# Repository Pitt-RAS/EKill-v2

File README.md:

# EKill-v2

This repository is part of the Pitt RAS effort for IARC Mission 7.  For an overview of the IARC competition as well as the team's efforts and technical approaches, check out our [team website](http://pittras.org/projects/IARC/), and in particular the [technical postmortem post for the project](http://pittras.org/projects/iarc/2018/08/10/update-iarc-technical-postmortem.html).

A new EKill board, slightly modifed from Liam's previous board to support more motors and handle unexpected errors on the PWM line.

To run the simulation files in Sim_Parts, you should be able to open KillSwitch2.asc from LTSpice XVII, and it should work. If you really want to understand how the logic works, the best way is to simply monitor the capacitor voltage and compare it with the PWM wave. Change the time that the PWM wave is on from 1.45 ms to 1.5 ms and back to see the timing threshold in action.

Similarly, I have the Eagle libraries organized the way they are so that anyone can simply open the main eagle project and have it just work. Though it does sacrifice some neatness.

If you want to see the parts that the footprints in the board files correspond to, open up the sole excel file in Sim_Parts.

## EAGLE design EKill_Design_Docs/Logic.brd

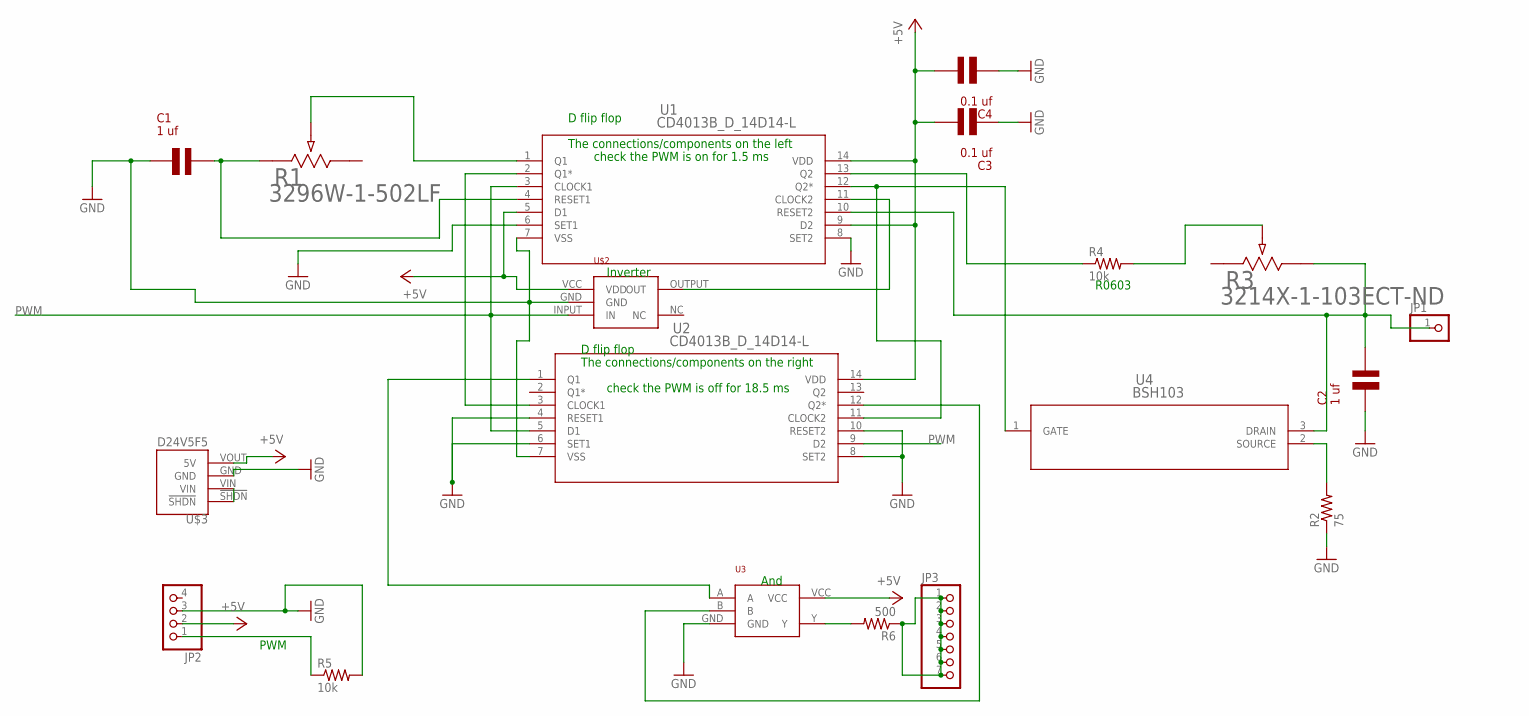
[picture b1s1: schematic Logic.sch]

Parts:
C1, C2: 1 uf; X7R0805
C3, C4: 0.1 uf; X7R0805
JP1: PINHD-1X1; 1X01
JP2: PINHD-1X4; 1X04
JP3: PINHD-1X7; 1X07
R1: 3296W-1-502LF; POT_3296W
R2: 75; R0603
R3: 3214X-1-103ECT-ND; POT_3214X
R4, R5: 10k; R0603
R6: 500; R0603
U1, U2: CD4013B_D_14D14-L; D14-L
U3: NC7SZ08-AND; NC7S04-SOT23
U4: BSH103; SOT23
U$2: NCS704-INVERTER; NC7S04-SOT23
U$3: D24V5F5; D24V5FX_FLAT_THIN_R

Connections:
+5V: C3.2, C4.2, JP2.2, U1.5 (D1), U1.9 (D2), U1.14 (VDD), U2.14 (VDD), U3.VCC, U$2.VCC (VDD), U$3.VOUT (5V)
GND: C1.1, C2.1, C3.1, C4.1, JP2.3, R2.1, R5.2, U1.6 (SET1), U1.7 (VSS), U1.8 (SET2), U2.4 (RESET1), U2.6 (SET1), U2.7 (VSS), U2.8 (SET2), U2.10 (RESET2), U3.GND, U$2.GND, U$3.GND
unnamed: R3.WIPER (2), R4.2
unnamed: C1.2, R1.1, U1.4 (RESET1)
unnamed: U1.11 (CLOCK2), U$2.OUTPUT (OUT)
unnamed: U1.2 (Q1*), U2.3 (CLOCK1)
unnamed: R4.1, U1.13 (Q2)
unnamed: R1.2, U1.1 (Q1)
unnamed: C2.2, JP1.1, R3.CW (3), U1.10 (RESET2), U4.3 (DRAIN)
unnamed: JP3.1, JP3.2, JP3.3, JP3.4, JP3.5, JP3.6, JP3.7, R6.1
unnamed: U1.12 (Q2*), U2.11 (CLOCK2), U4.1 (GATE)
unnamed: U2.1 (Q1), U3.A
unnamed: U2.12 (Q2*), U3.B
unnamed: R6.2, U3.Y
unnamed: U$3.!SHDN, U$3.VIN
unnamed: R2.2, U4.2 (SOURCE)
PWM: JP2.1, R5.1, U1.3 (CLOCK1), U2.5 (D1), U2.9 (D2), U$2.INPUT (IN)

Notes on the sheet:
Inverter
And
D flip flop
The connections/components on the left
check the PWM is on for 1.5 ms
check the PWM is off for 18.5 ms
The connections/components on the right
R0603
PWM

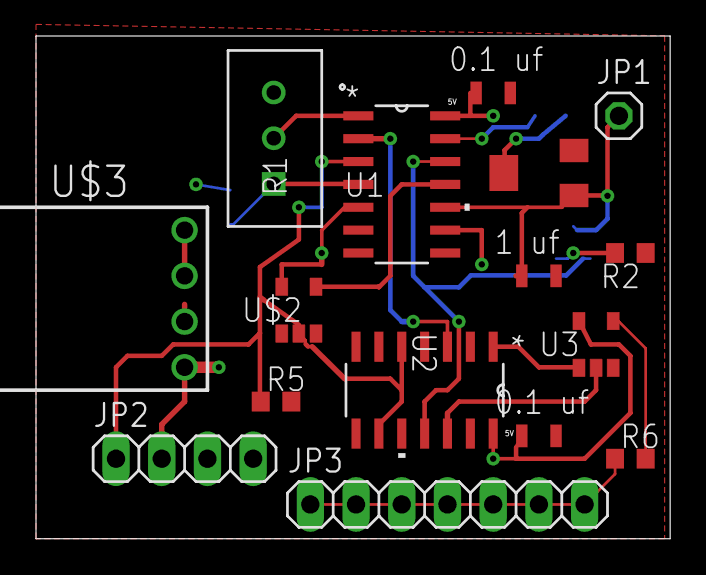
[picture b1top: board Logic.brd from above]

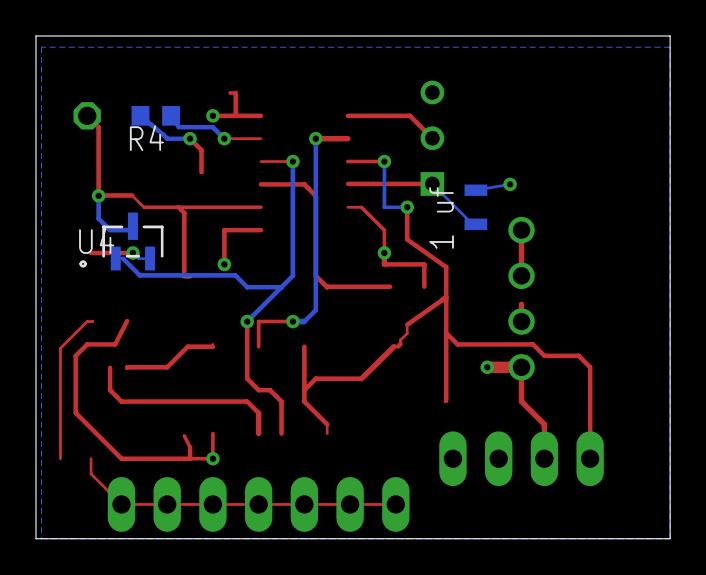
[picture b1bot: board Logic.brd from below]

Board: 2 copper layers, 35.2 x 27.9 mm, 19 parts (3 on the bottom side), 17 nets.

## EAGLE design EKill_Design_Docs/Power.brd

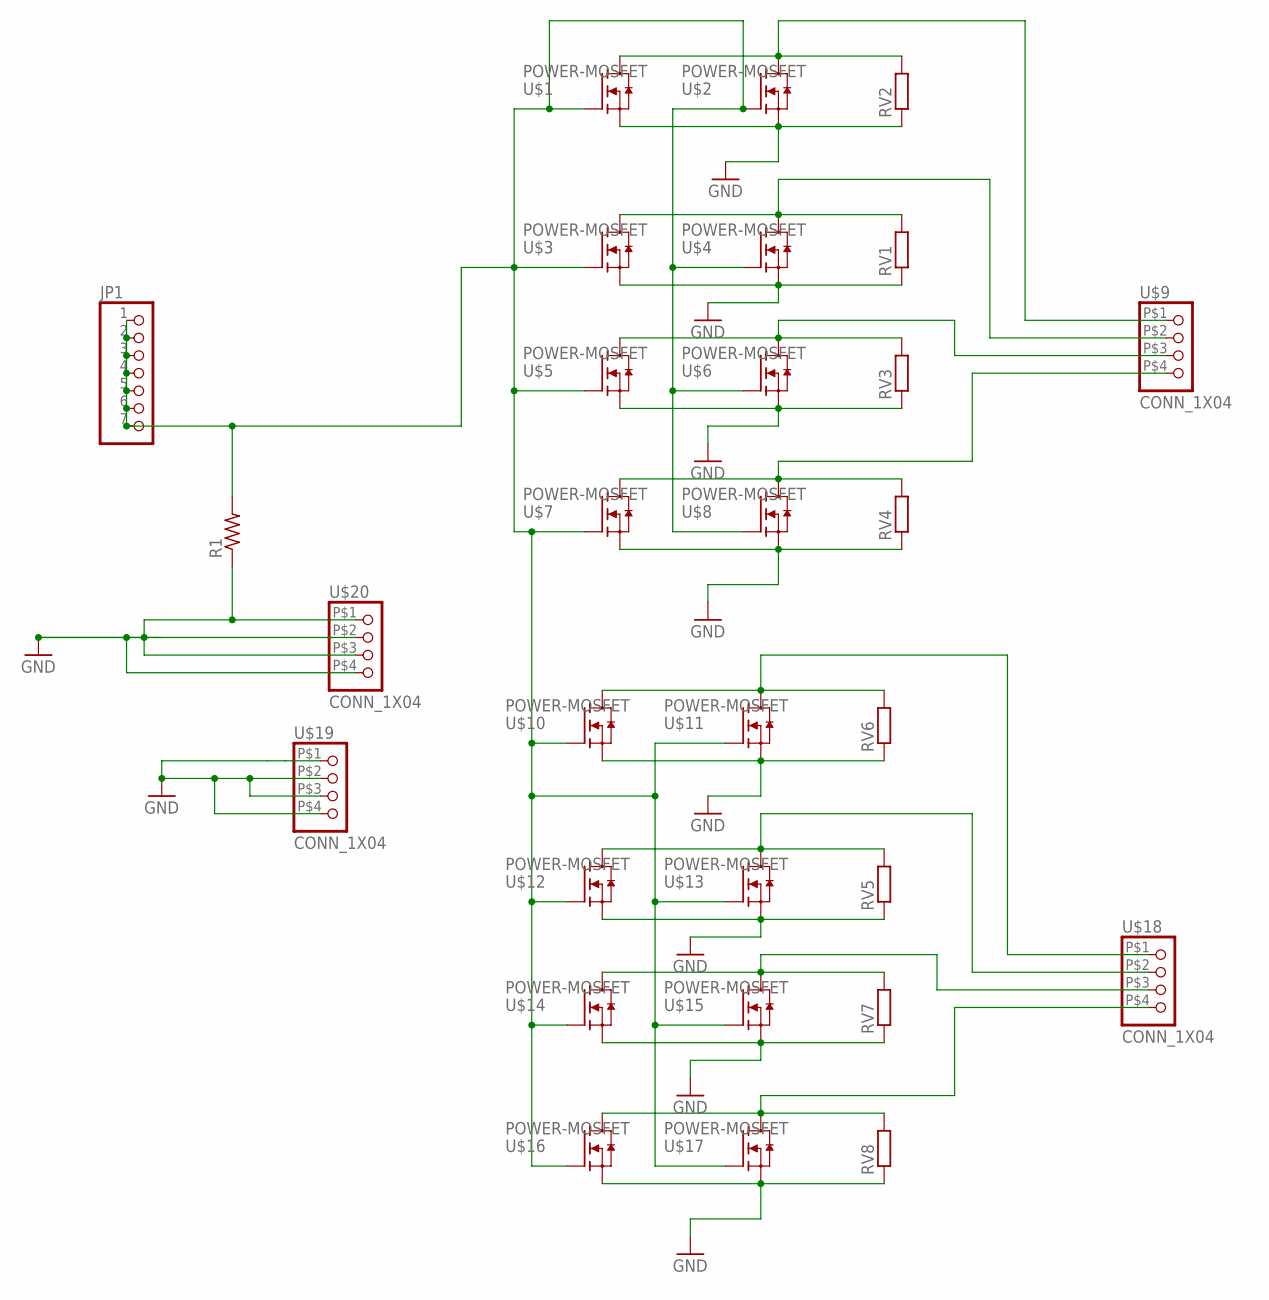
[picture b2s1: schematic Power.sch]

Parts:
JP1: PINHD-1X7; 1X07
R1: R-US_R0603; R0603
RV1, RV2, RV3, RV4, RV5, RV6, RV7, RV8: R-EU_R1210; R1210
U$1, U$2, U$3, U$4, U$5, U$6, U$7, U$8, U$10, U$11, U$12, U$13, U$14, U$15, U$16, U$17: POWER-MOSFET; BSC010N04LS
U$9, U$18, U$19, U$20: CONN_1X04

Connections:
GND: R1.1, RV1.1, RV2.1, RV3.1, RV4.1, RV5.1, RV6.1, RV7.1, RV8.1, U$1.P$3 (S), U$1.S, U$2.P$3 (S), U$2.S, U$3.P$3 (S), U$3.S, U$4.P$3 (S), U$4.S, U$5.P$3 (S), U$5.S, U$6.P$3 (S), U$6.S, U$7.P$3 (S), U$7.S, U$8.P$3 (S), U$8.S, U$10.P$3 (S), U$10.S, U$11.P$3 (S), U$11.S, U$12.P$3 (S), U$12.S, U$13.P$3 (S), U$13.S, U$14.P$3 (S), U$14.S, U$15.P$3 (S), U$15.S, U$16.P$3 (S), U$16.S, U$17.P$3 (S), U$17.S, U$19.P$1 (1), U$19.P$2 (2), U$19.P$3 (3), U$19.P$4 (4), U$20.P$1 (1), U$20.P$2 (2), U$20.P$3 (3), U$20.P$4 (4)
unnamed: RV2.2, U$1.D, U$1.P$1 (D), U$1.P$2 (D), U$1.P$4 (D), U$1.P$5 (D), U$1.P$6 (D), U$1.P$7 (D), U$2.D, U$2.P$1 (D), U$2.P$2 (D), U$2.P$4 (D), U$2.P$5 (D), U$2.P$6 (D), U$2.P$7 (D), U$9.P$1 (1)
unnamed: RV6.2, U$10.D, U$10.P$1 (D), U$10.P$2 (D), U$10.P$4 (D), U$10.P$5 (D), U$10.P$6 (D), U$10.P$7 (D), U$11.D, U$11.P$1 (D), U$11.P$2 (D), U$11.P$4 (D), U$11.P$5 (D), U$11.P$6 (D), U$11.P$7 (D), U$18.P$1 (1)
unnamed: RV5.2, U$12.D, U$12.P$1 (D), U$12.P$2 (D), U$12.P$4 (D), U$12.P$5 (D), U$12.P$6 (D), U$12.P$7 (D), U$13.D, U$13.P$1 (D), U$13.P$2 (D), U$13.P$4 (D), U$13.P$5 (D), U$13.P$6 (D), U$13.P$7 (D), U$18.P$2 (2)
unnamed: RV7.2, U$14.D, U$14.P$1 (D), U$14.P$2 (D), U$14.P$4 (D), U$14.P$5 (D), U$14.P$6 (D), U$14.P$7 (D), U$15.D, U$15.P$1 (D), U$15.P$2 (D), U$15.P$4 (D), U$15.P$5 (D), U$15.P$6 (D), U$15.P$7 (D), U$18.P$3 (3)
unnamed: RV1.2, U$3.D, U$3.P$1 (D), U$3.P$2 (D), U$3.P$4 (D), U$3.P$5 (D), U$3.P$6 (D), U$3.P$7 (D), U$4.D, U$4.P$1 (D), U$4.P$2 (D), U$4.P$4 (D), U$4.P$5 (D), U$4.P$6 (D), U$4.P$7 (D), U$9.P$2 (2)
unnamed: RV3.2, U$5.D, U$5.P$1 (D), U$5.P$2 (D), U$5.P$4 (D), U$5.P$5 (D), U$5.P$6 (D), U$5.P$7 (D), U$6.D, U$6.P$1 (D), U$6.P$2 (D), U$6.P$4 (D), U$6.P$5 (D), U$6.P$6 (D), U$6.P$7 (D), U$9.P$3 (3)
unnamed: RV8.2, U$16.D, U$16.P$1 (D), U$16.P$2 (D), U$16.P$4 (D), U$16.P$5 (D), U$16.P$6 (D), U$16.P$7 (D), U$17.D, U$17.P$1 (D), U$17.P$2 (D), U$17.P$4 (D), U$17.P$5 (D), U$17.P$6 (D), U$17.P$7 (D), U$18.P$4 (4)
unnamed: RV4.2, U$7.D, U$7.P$1 (D), U$7.P$2 (D), U$7.P$4 (D), U$7.P$5 (D), U$7.P$6 (D), U$7.P$7 (D), U$8.D, U$8.P$1 (D), U$8.P$2 (D), U$8.P$4 (D), U$8.P$5 (D), U$8.P$6 (D), U$8.P$7 (D), U$9.P$4 (4)
unnamed: JP1.1, JP1.2, JP1.3, JP1.4, JP1.5, JP1.6, JP1.7, R1.2, U$1.G, U$2.G, U$3.G, U$4.G, U$5.G, U$6.G, U$7.G, U$8.G, U$10.G, U$11.G, U$12.G, U$13.G, U$14.G, U$15.G, U$16.G, U$17.G

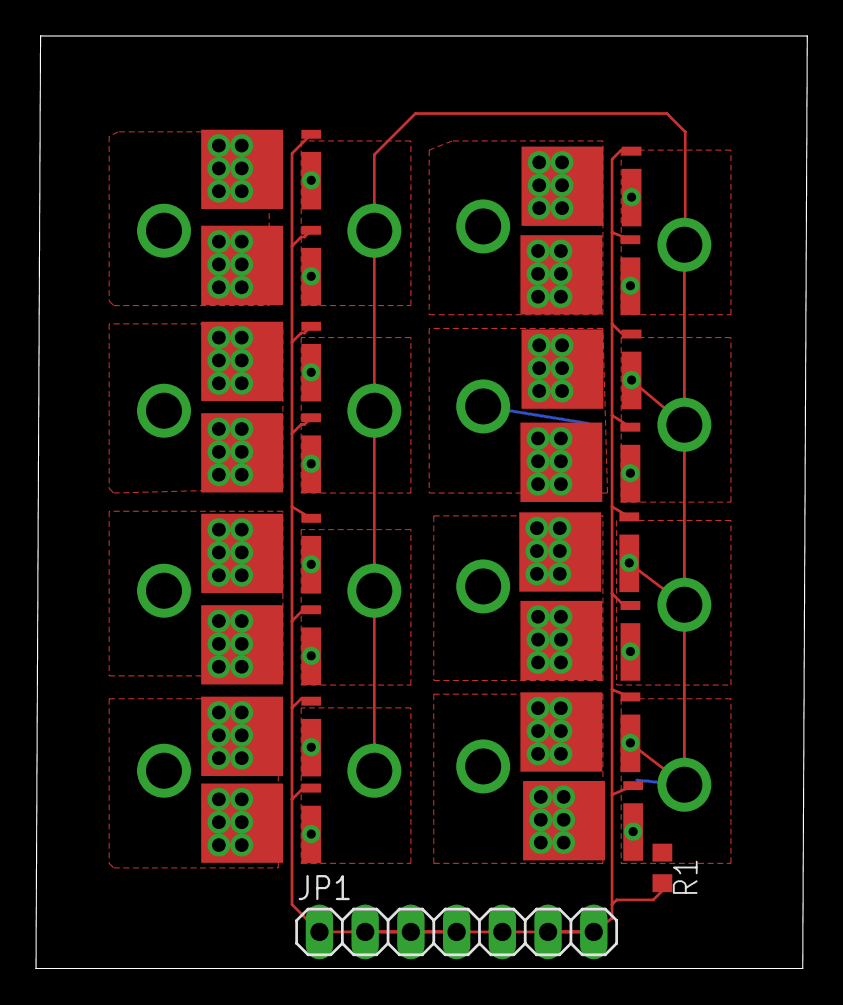
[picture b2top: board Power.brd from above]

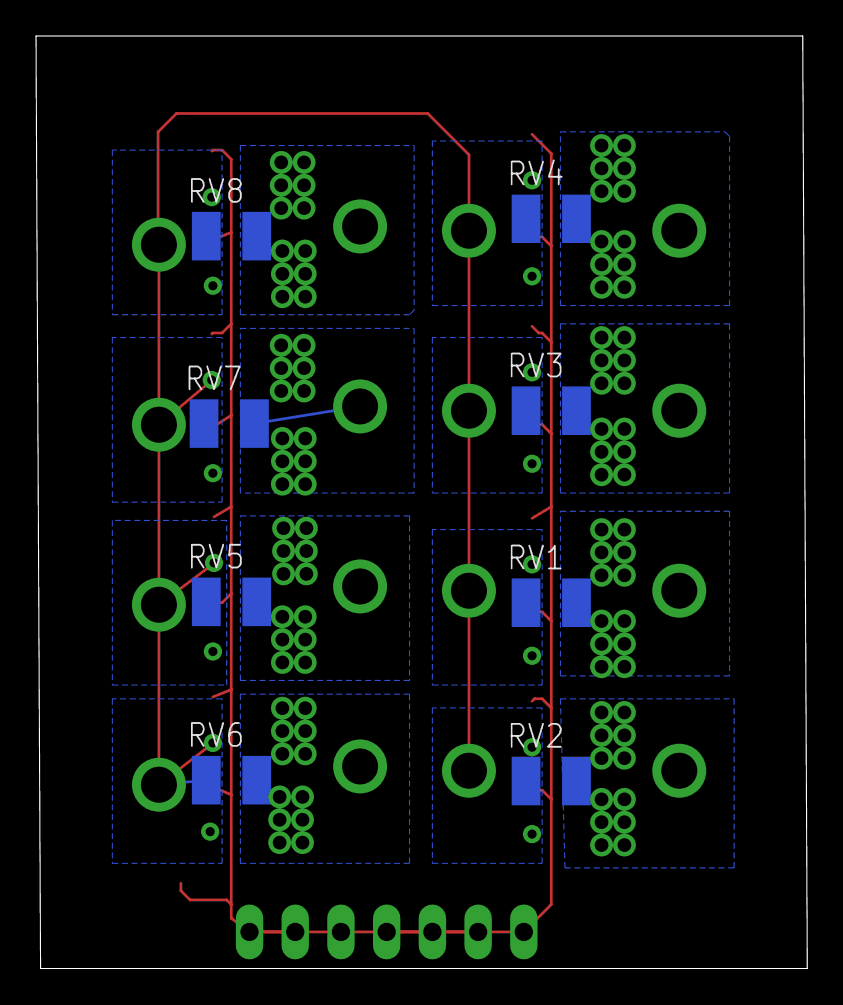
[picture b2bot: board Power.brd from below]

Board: 2 copper layers, 42.9 x 51.8 mm, 30 parts (8 on the bottom side), 10 nets.

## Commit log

2018-02-02 Creating a new directory
    Because Windows is annoying
2018-02-02 Another new directory
2018-02-02 Added necessary library/design files
    If you want the parts corresponding to the library files, head over to /Sim_Parts and look in the excel file.
    I apologize in advance for how beautiful my schematics are.
2018-02-02 Files for parts and simulation
    The simulation was run on LTSpice XVII.
